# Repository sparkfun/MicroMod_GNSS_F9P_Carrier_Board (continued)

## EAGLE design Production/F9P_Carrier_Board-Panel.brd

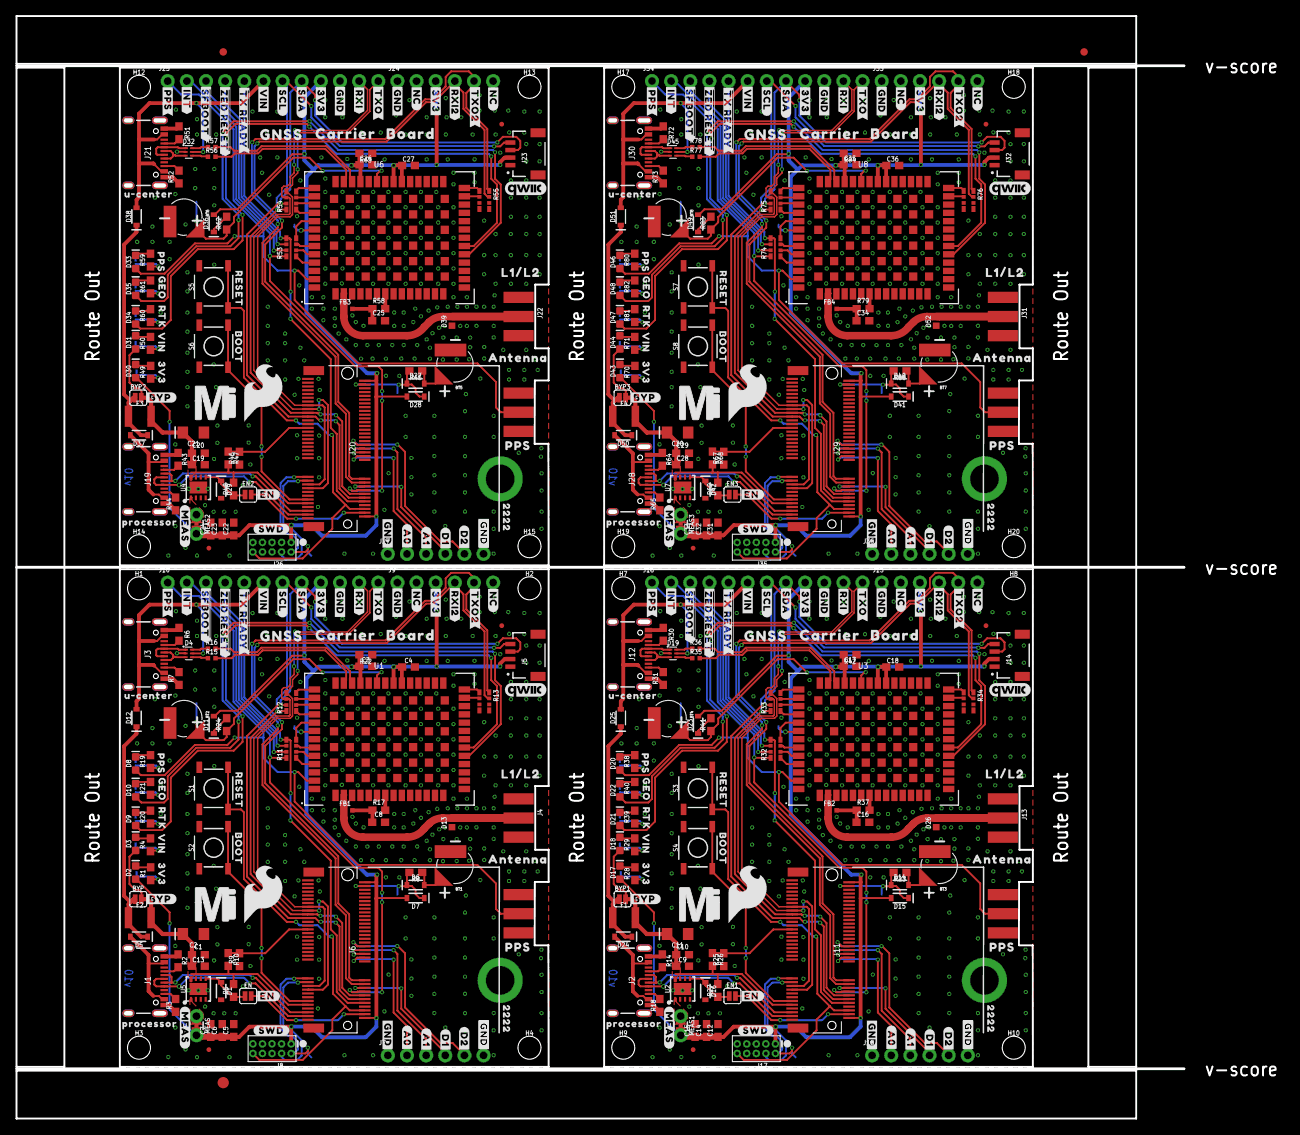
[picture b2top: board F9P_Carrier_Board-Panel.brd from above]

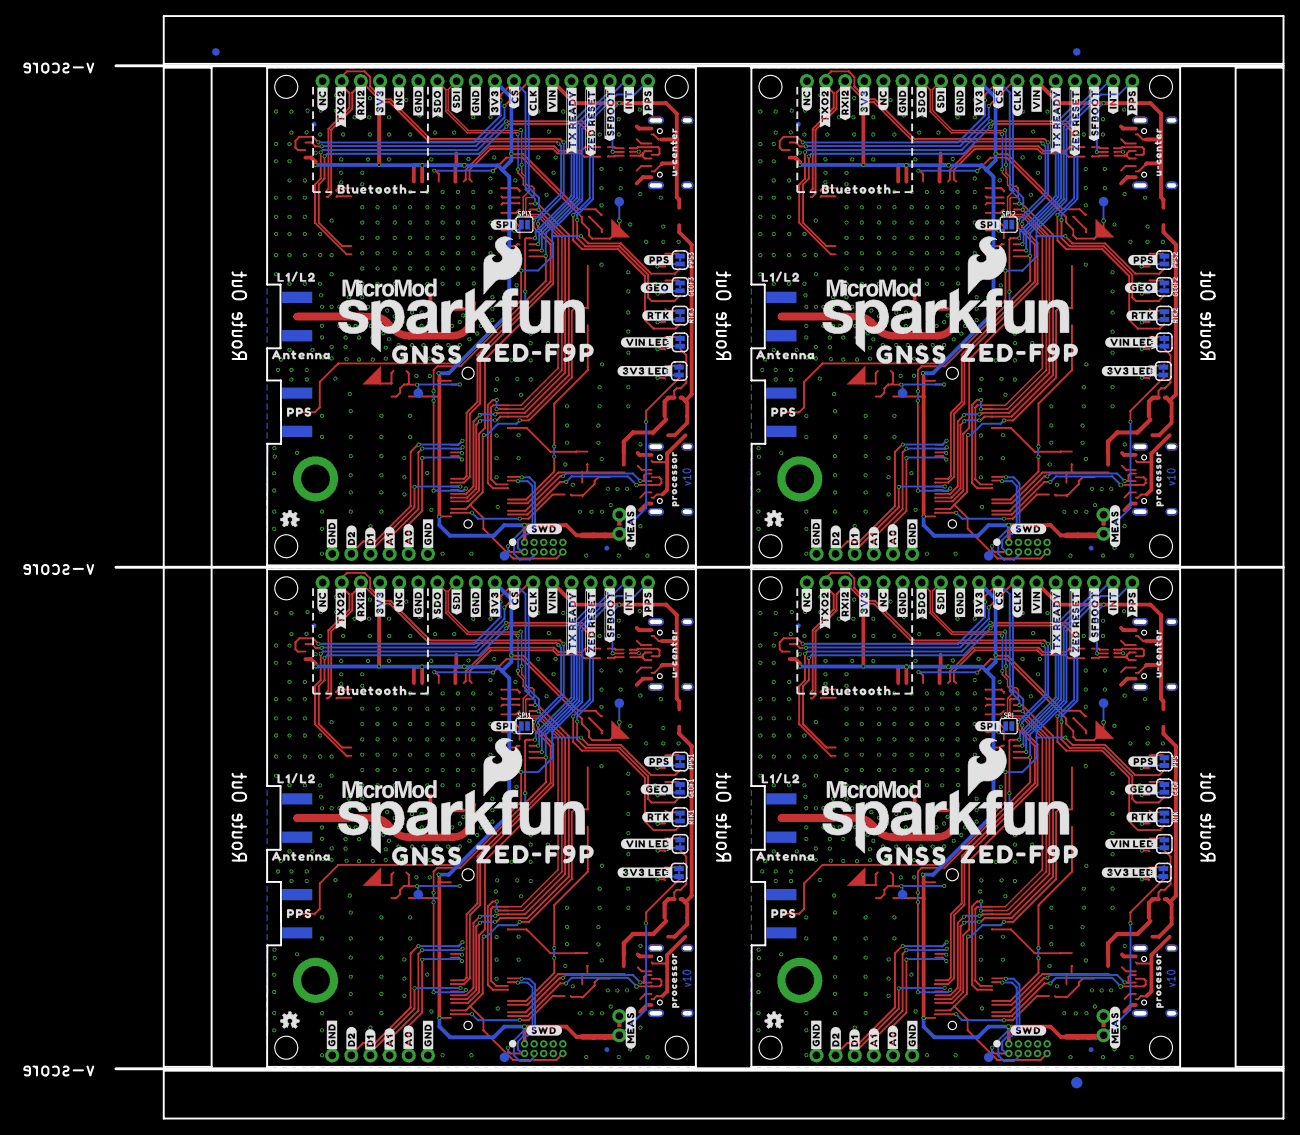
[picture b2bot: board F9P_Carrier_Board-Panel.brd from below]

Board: 2 copper layers, 154.9 x 146.3 mm, 698 parts (219 on the bottom side), 284 nets.

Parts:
3V1, 3V2, 3V3, 3V4: JUMPER-SMT_2_NC_TRACE_SILK; SMT-JUMPER_2_NC_TRACE_SILK
BT1, BT3, BT5, BT7: ML414H; ML414H_IV01E
BT2, BT4, BT6, BT8: ML414H_IV01E_BATTERY; ML414H_IV01E
BYP, BYP1, BYP2, BYP3: JUMPER-SMT_2_NO_SILK; SMT-JUMPER_2_NO_SILK
C1, C3, C4, C6, C10, C14, C17, C18, C20, C23, C26, C27, C29, C32, C35, C36: 0.1uF; 0603
C2, C11, C21, C30: 10uF; EIA3216
C5, C12, C22, C31: 1.0uF; 0603
C7, C9, C13, C15, C19, C24, C28, C33: 0.22uF; 0603
C8, C16, C25, C34: 47pF; 0603
D1, D16, D29, D42: 3.3V; SOD-323
D2, D3, D17, D18, D30, D31, D43, D44: RED; LED-0603
D4, D19, D32, D45: PRTR5V0U2F; SOT886
D5, D6, D12, D14, D24, D25, D27, D37, D38, D40, D50, D51: 3A/10V/280mV; SOD-323
D7, D15, D28, D41: 1A/23V/620mV; SOD-323
D8, D9, D10, D20, D21, D22, D33, D34, D35, D46, D47, D48: BLUE; LED-0603
D11, D23, D36, D49: 0.5A/40V/420mV; SOD-323
D13, D26, D39, D52: PESD0402; 0402
E1, E2, E3, E4: ANTENNA-SMA-GROUNDEDEDGE_SMA; SMA-EDGE
E$1, E$2, E$3, E$4: FIDUCIAL-1X2
E$5, E$6: FIDUCIAL-1.5X3
EN, EN1, EN2, EN3: JUMPER-SMT_2_NO_SILK; SMT-JUMPER_2_NO_SILK
F1, F2, F3, F4: 6V/2A; 1210
FB1, FB2, FB3, FB4: FERRITE_BEAD-120_OHM-0402T; 0402-TIGHT
FD1, FD2, FD3, FD4, FD5, FD6, FD7, FD8, FD9, FD10, FD11, FD12, FD13, FD14, FD15, FD16: FIDUCIALUFIDUCIAL; FIDUCIAL-MICRO
GEOF, GEOF1, GEOF2, GEOF3: JUMPER-SMT_2_NC_TRACE_SILK; SMT-JUMPER_2_NC_TRACE_SILK
H1, H2, H3, H4, H7, H8, H9, H10, H12, H13, H14, H15, H17, H18, H19, H20: STAND-OFFTIGHT; STAND-OFF-TIGHT
H5, H6, H11, H16: STAND-OFF-REFLOW-M2.5_2.5MM_TALL; STAND-OFF-REFLOW-M2.5
J1, J2, J3, J12, J19, J21, J28, J30: USB-C-16P-2LAYER-PADS
J4, J13, J22, J31: U.FL; SMA-EDGE
J5, J14, J23, J32: QWIIC_RIGHT_ANGLE; JST04_1MM_RA
J6, J11, J20, J29: MICROMOD-2222-C; M.2-CONNECTOR-E
J7, J9, J15, J18, J24, J27, J33, J36: 1X06_NO_SILK
J8, J17, J26, J35: JTAG; 2X5-PTH-1.27MM
J10, J16, J25, J34: 1X12_NO_SILK
LOGO1, LOGO4, LOGO6, LOGO8: SFE_LOGO_NAME_FLAME.3_INCH; SFE_LOGO_NAME_FLAME_.3
LOGO2, LOGO3, LOGO5, LOGO7: OSHW-LOGOMINI; OSHW-LOGO-MINI
MEAS, MEAS1, MEAS2, MEAS3: JUMPER-COMBO_2_NC_TRACE; COMBO-JUMPER_2_NC_TRACE
PPS, PPS1, PPS2, PPS3: JUMPER-SMT_2_NC_TRACE_SILK; SMT-JUMPER_2_NC_TRACE_SILK
R1, R4, R8, R19, R20, R21, R23, R28, R29, R38, R39, R40, R45, R49, R50, R59, R60, R61, R66, R70, R71, R80, R81, R82: 1k; 0603
R2, R3, R6, R7, R14, R18, R30, R31, R43, R44, R51, R52, R64, R65, R72, R73: 5.1k; 0603
R5, R22, R27, R42, R48, R63, R69, R84: 100k; 0603
R9, R25, R46, R67: 10k; 0603
R10, R26, R47, R68: 20k; 0603
R11, R12, R13, R32, R33, R34, R53, R54, R55, R74, R75, R76: 33; 1206_RA
R15, R16, R35, R36, R56, R57, R77, R78: 27OHM; 0402-TIGHT
R17, R37, R58, R79: 33; 0603
R24, R41, R62, R83: 3.3k; 0603
RTK, RTK1, RTK2, RTK3: JUMPER-SMT_2_NC_TRACE_SILK; SMT-JUMPER_2_NC_TRACE_SILK
S1, S3, S5, S7: Reset; TACTILE_SWITCH_SMD_5.2MM
S2, S4, S6, S8: BOOT; TACTILE_SWITCH_SMD_5.2MM
SPI, SPI1, SPI2, SPI3: JUMPER-SMT_2_NO_SILK; SMT-JUMPER_2_NO_SILK
TP1, TP2, TP3, TP4, TP5, TP6, TP7, TP8, TP9, TP10, TP11, TP12: TEST-POINT3X5; PAD.03X.05
U1, U3, U6, U8: U-BLOX_ZED-F9P; ZED-F9P
U2, U4, U5, U7: AP7361C-33; UDFN-8
U$1, U$150, U$239, U$328: ##SFBOOT##13
U$2, U$151, U$240, U$329: ##SFBOOT##8
U$3, U$4, U$31, U$32, U$98, U$99, U$113, U$114, U$191, U$192, U$206, U$207, U$280, U$281, U$295, U$296: #3V3#1
U$5, U$87, U$180, U$269: #RESET10
U$6, U$7, U$33, U$34, U$64, U$65, U$66, U$77, U$78, U$100, U$101, U$115, U$116, U$155, U$156, U$157, U$168, U$169, U$193, U$194, U$208, U$209, U$244, U$245, U$246, U$257, U$258, U$282, U$283, U$297, U$298, U$333, U$334, U$335, U$346, U$347: #GND#0
U$8, U$119, U$212, U$301: ##TX_READY##13
U$9, U$102, U$195, U$284: #PPS#6
U$10, U$128, U$221, U$310: #SCL#1
U$11, U$103, U$196, U$285: #RXI2#9
U$12, U$129, U$222, U$311: #SDA#0
U$13, U$130, U$223, U$312: #TXO#5
U$14, U$135, U$224, U$313: #RXI#6
U$15, U$104, U$197, U$286: #TXO2#9
U$16, U$136, U$225, U$314: PPS15
U$17, U$35, U$105, U$117, U$198, U$210, U$287, U$299: #VIN#13
U$18, U$106, U$199, U$288: GEO15
U$19, U$107, U$200, U$289: PPS14
U$20, U$108, U$201, U$290: RTK16
U$21, U$137, U$226, U$315: ANTENNA16
U$22, U$138, U$227, U$316: L1#L216
U$23, U$109, U$202, U$291: #GEO#9
U$24, U$120, U$213, U$302: ##TX_READY##7
U$25, U$152, U$241, U$330: MICROMOD_LOGO_.5
U$26, U$110, U$203, U$292: #PPS#10
U$27, U$111, U$204, U$293: #RTK#8
U$28, U$139, U$228, U$317: ##CS##9
U$29, U$121, U$214, U$303: #INT#4
U$30, U$112, U$205, U$294: #SPI#11
U$36, U$118, U$211, U$300: #INT#10
U$37, U$122, U$215, U$304: #PPS#3
U$38, U$123, U$216, U$305: #TXO2#10
U$39, U$86, U$179, U$268: #BYP#8
U$40, U$124, U$217, U$306: #RXI2#10
U$41, U$153, U$242, U$331: MICROMOD_MI_LOGO_1
U$42, U$89, U$94, U$132, U$182, U$187, U$271, U$276: #MEAS#10
U$43, U$88, U$181, U$270: BOOT10
U$44, U$125, U$218, U$307: ZED#F9P19
U$45, U$170, U$259, U$348: GNSS21
U$46, U$140, U$229, U$318: #CLK#7
U$47, U$141, U$230, U$319: #SDO#9
U$48, U$97, U$190, U$279: #EN#0
U$49, U$126, U$219, U$308: U#CENTER20
U$50, U$127, U$220, U$309: QWIIC_5.5MM
U$51, U$90, U$93, U$131, U$183, U$186, U$272, U$275: #SWD#10
U$52, U$73, U$162, U$163, U$251, U$252, U$340, U$341: PROCESSOR23
U$53, U$142, U$231, U$320: #SDI#11
U$54, U$143, U$232, U$321: BLUETOOTH24
U$55, U$83, U$175, U$176, U$264, U$265, U$353, U$354: #NC#4
U$56, U$144, U$233, U$322: U#CENTER22
U$57, U$164, U$253, U$342: #A0#14
U$58, U$145, U$234, U$323: L1#L217
U$59, U$146, U$235, U$324: ANTENNA17
U$60, U$147, U$236, U$325: PPS16
U$61, U$148, U$237, U$326: ##ZED_RESET##9
U$62, U$149, U$238, U$327: ##ZED_RESET##14
U$63, U$154, U$243, U$332: SFE_LOGO_FLAME_.3
U$67, U$158, U$247, U$336: #A0#8
U$68, U$91, U$184, U$273: VIN3
U$69, U$92, U$185, U$274: 3V34
U$70, U$159, U$248, U$337: #A1#8
U$71, U$160, U$249, U$338: #D1#8
U$72, U$161, U$250, U$339: #D2#8
U$74, U$165, U$254, U$343: #A1#14
U$75, U$166, U$255, U$344: #D1#14
U$76, U$167, U$256, U$345: #D2#14
U$79, U$171, U$260, U$349: GNSS501
U$80, U$172, U$261, U$350: CARRIER502
U$81, U$173, U$262, U$351: BOARD503
U$82, U$174, U$263, U$352: 2222501
U$84, U$85, U$177, U$178, U$266, U$267, U$355, U$356: #NC#5
U$95, U$133, U$188, U$277: #VIN_LED#10
U$96, U$134, U$189, U$278: #3V3_LED#10
VIN, VIN1, VIN2, VIN3: JUMPER-SMT_2_NC_TRACE_SILK; SMT-JUMPER_2_NC_TRACE_SILK

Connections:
3.3V: C3.1, C4.1, C5.1, C6.1, C7.1, D2.A, D7.A, D11.A, J5.2, J6.2, J6.74, J8.1, J9.3, J10.9, MEAS.2, MEAS.4, R22.2, U1.33, U1.34, U1.38
3.3V1: C12.1, C14.1, C15.1, C17.1, C18.1, D15.A, D17.A, D23.A, J11.2, J11.74, J14.2, J15.3, J16.9, J17.1, MEAS1.2, MEAS1.4, R42.2, U3.33, U3.34, U3.38
3.3V2: C22.1, C23.1, C24.1, C26.1, C27.1, D28.A, D30.A, D36.A, J20.2, J20.74, J23.2, J24.3, J25.9, J26.1, MEAS2.2, MEAS2.4, R63.2, U6.33, U6.34, U6.38
3.3V3: C31.1, C32.1, C33.1, C35.1, C36.1, D41.A, D43.A, D49.A, J29.2, J29.74, J32.2, J33.3, J34.9, J35.1, MEAS3.2, MEAS3.4, R84.2, U8.33, U8.34, U8.38
3.3V_EN: D1.C, EN.1, R5.1, U5.5
3.3V_EN1: D16.C, EN1.1, R27.1, U2.5
3.3V_EN2: D29.C, EN2.1, R48.1, U4.5
3.3V_EN3: D42.C, EN3.1, R69.1, U7.5
!BOOT!: J6.11, S2.3, S2.4
!BOOT!1: J11.11, S4.3, S4.4
!BOOT!2: J20.11, S6.3, S6.4
!BOOT!3: J29.11, S8.3, S8.4
!RESET!: J6.6, J8.10, S1.3, S1.4
!RESET!1: J11.6, J17.10, S3.3, S3.4
!RESET!2: J20.6, J26.10, S5.3, S5.4
!RESET!3: J29.6, J35.10, S7.3, S7.4
!SAFEBOOT!: J10.3, R11.P7
!SAFEBOOT!1: J16.3, R32.P7
!SAFEBOOT!2: J25.3, R53.P7
!SAFEBOOT!3: J34.3, R74.P7
!ZED_RESET!: J10.4, R11.P6
!ZED_RESET!1: J16.4, R32.P6
!ZED_RESET!2: J25.4, R53.P6
!ZED_RESET!3: J34.4, R74.P6
A0: J6.34, J7.2
A1: J6.38, J7.3
A2: J11.38, J18.3
A3: J11.34, J18.2
A4: J20.38, J27.3
A5: J20.34, J27.2
A6: J29.38, J36.3
A7: J29.34, J36.2
D1: J6.18, J7.4
D2: J11.18, J18.4
D3: J20.18, J27.4
D4: J29.18, J36.4
D_SEL: SPI.1, U1.47
D_SEL1: SPI1.1, U3.47
D_SEL2: SPI2.1, U6.47
D_SEL3: SPI3.1, U8.47
G0/D1: J11.40, J18.5
G0/D2: J6.40, J7.5
G0/D3: J20.40, J27.5
G0/D4: J29.40, J36.5
GEO_STAT: D10.A, U1.19
GEO_STAT1: D22.A, U3.19
GEO_STAT2: D35.A, U6.19
GEO_STAT3: D48.A, U8.19
GND: 3V3.2, BT1.-, BT2.-, C1.2, C2.-, C3.2, C4.2, C5.2, C6.2, C7.2, C8.2, C13.2, D1.A, D4.2, D13.1, E1.GND@0, E1.GND@1, E1.GND@2, E1.GND@3, GEOF.1, H5.1, J1.GND, J1.GND2, J3.GND, J3.GND2, J4.GND@0, J4.GND@1, J4.GND@2, J4.GND@3, J5.1, J6.1, J6.7, J6.33, J6.36, J6.39, J6.45, J6.75, J7.1, J7.6, J8.3, J8.5, J8.9, J9.1, J10.10, PPS.1, R2.1, R3.1, R6.1, R7.1, R9.1, R22.1, RTK.1, S1.1, S1.2, S2.1, S2.2, SPI.2, U1.1, U1.3, U1.12, U1.14, U1.32, U1.37, U1.41, U1.48, U1.55, U1.56, U1.57, U1.58, U1.59, U1.60, U1.61, U1.62, U1.63, U1.64, U1.65, U1.66, U1.67, U1.68, U1.69, U1.70, U1.71, U1.72, U1.73, U1.74, U1.75, U1.76, U1.77, U1.78, U1.79, U1.80, U1.81, U1.82, U1.83, U1.84, U1.85, U1.86, U1.87, U1.88, U1.89, U1.90, U1.91, U1.92, U1.93, U1.94, U1.95, U1.96, U1.97, U1.98, U1.99, U1.100, U1.101, U1.102, U5.4, U5.EP, VIN.2
GND1: 3V1.2, BT3.-, BT4.-, C9.2, C10.2, C11.-, C12.2, C14.2, C15.2, C16.2, C17.2, C18.2, D16.A, D19.2, D26.1, E2.GND@0, E2.GND@1, E2.GND@2, E2.GND@3, GEOF1.1, H6.1, J2.GND, J2.GND2, J11.1, J11.7, J11.33, J11.36, J11.39, J11.45, J11.75, J12.GND, J12.GND2, J13.GND@0, J13.GND@1, J13.GND@2, J13.GND@3, J14.1, J15.1, J16.10, J17.3, J17.5, J17.9, J18.1, J18.6, PPS1.1, R14.1, R18.1, R25.1, R30.1, R31.1, R42.1, RTK1.1, S3.1, S3.2, S4.1, S4.2, SPI1.2, U2.4, U2.EP, U3.1, U3.3, U3.12, U3.14, U3.32, U3.37, U3.41, U3.48, U3.55, U3.56, U3.57, U3.58, U3.59, U3.60, U3.61, U3.62, U3.63, U3.64, U3.65, U3.66, U3.67, U3.68, U3.69, U3.70, U3.71, U3.72, U3.73, U3.74, U3.75, U3.76, U3.77, U3.78, U3.79, U3.80, U3.81, U3.82, U3.83, U3.84, U3.85, U3.86, U3.87, U3.88, U3.89, U3.90, U3.91, U3.92, U3.93, U3.94, U3.95, U3.96, U3.97, U3.98, U3.99, U3.100, U3.101, U3.102, VIN1.2
GND2: 3V2.2, BT5.-, BT6.-, C19.2, C20.2, C21.-, C22.2, C23.2, C24.2, C25.2, C26.2, C27.2, D29.A, D32.2, D39.1, E3.GND@0, E3.GND@1, E3.GND@2, E3.GND@3, GEOF2.1, H11.1, J19.GND, J19.GND2, J20.1, J20.7, J20.33, J20.36, J20.39, J20.45, J20.75, J21.GND, J21.GND2, J22.GND@0, J22.GND@1, J22.GND@2, J22.GND@3, J23.1, J24.1, J25.10, J26.3, J26.5, J26.9, J27.1, J27.6, PPS2.1, R43.1, R44.1, R46.1, R51.1, R52.1, R63.1, RTK2.1, S5.1, S5.2, S6.1, S6.2, SPI2.2, U4.4, U4.EP, U6.1, U6.3, U6.12, U6.14, U6.32, U6.37, U6.41, U6.48, U6.55, U6.56, U6.57, U6.58, U6.59, U6.60, U6.61, U6.62, U6.63, U6.64, U6.65, U6.66, U6.67, U6.68, U6.69, U6.70, U6.71, U6.72, U6.73, U6.74, U6.75, U6.76, U6.77, U6.78, U6.79, U6.80, U6.81, U6.82, U6.83, U6.84, U6.85, U6.86, U6.87, U6.88, U6.89, U6.90, U6.91, U6.92, U6.93, U6.94, U6.95, U6.96, U6.97, U6.98, U6.99, U6.100, U6.101, U6.102, VIN2.2
GND3: 3V4.2, BT7.-, BT8.-, C28.2, C29.2, C30.-, C31.2, C32.2, C33.2, C34.2, C35.2, C36.2, D42.A, D45.2, D52.1, E4.GND@0, E4.GND@1, E4.GND@2, E4.GND@3, GEOF3.1, H16.1, J28.GND, J28.GND2, J29.1, J29.7, J29.33, J29.36, J29.39, J29.45, J29.75, J30.GND, J30.GND2, J31.GND@0, J31.GND@1, J31.GND@2, J31.GND@3, J32.1, J33.1, J34.10, J35.3, J35.5, J35.9, J36.1, J36.6, PPS3.1, R64.1, R65.1, R67.1, R72.1, R73.1, R84.1, RTK3.1, S7.1, S7.2, S8.1, S8.2, SPI3.2, U7.4, U7.EP, U8.1, U8.3, U8.12, U8.14, U8.32, U8.37, U8.41, U8.48, U8.55, U8.56, U8.57, U8.58, U8.59, U8.60, U8.61, U8.62, U8.63, U8.64, U8.65, U8.66, U8.67, U8.68, U8.69, U8.70, U8.71, U8.72, U8.73, U8.74, U8.75, U8.76, U8.77, U8.78, U8.79, U8.80, U8.81, U8.82, U8.83, U8.84, U8.85, U8.86, U8.87, U8.88, U8.89, U8.90, U8.91, U8.92, U8.93, U8.94, U8.95, U8.96, U8.97, U8.98, U8.99, U8.100, U8.101, U8.102, VIN3.2
INT: J6.16, J10.2, R11.P8
INT1: J11.16, J16.2, R32.P8
INT2: J20.16, J25.2, R53.P8
INT3: J29.16, J34.2, R74.P8
unnamed: D2.C, R1.2
unnamed: R4.1, VIN.1
unnamed: 3V3.1, R1.1
unnamed: D3.C, R4.2
unnamed: EN.2, J6.4
unnamed: J3.A5, R6.2
unnamed: J3.B5, R7.2
unnamed: R20.1, RTK.2
unnamed: D4.6, R16.1
unnamed: J1.A5, R2.2
unnamed: J1.B5, R3.2
unnamed: D4.3, J3.A6, J3.B6
unnamed: D4.1, J3.A7, J3.B7
unnamed: BT1.+, D6.A, R8.1
unnamed: R11.P1, U1.51
unnamed: R11.P2, U1.50
unnamed: D4.4, R15.1
unnamed: C8.1, FB1.2, R17.1
unnamed: R11.P3, U1.49
unnamed: R11.P4, U1.46
unnamed: R12.P1, U1.45
unnamed: R12.P2, U1.44
unnamed: R12.P3, U1.43
unnamed: R12.P4, U1.42
unnamed: R13.P1, U1.27
unnamed: R13.P2, U1.26
unnamed: PPS.2, R19.1
unnamed: D8.C, R19.2
unnamed: D9.C, R20.2
unnamed: J2.A5, R14.2
unnamed: J2.B5, R18.2
unnamed: D11.C, R24.2
unnamed: BT3.+, D14.A, R23.1
unnamed: EN1.2, J11.4
unnamed: J12.A5, R30.2
unnamed: J12.B5, R31.2
unnamed: D19.3, J12.A6, J12.B6
unnamed: D19.1, J12.A7, J12.B7
unnamed: R34.P1, U3.27
unnamed: R34.P2, U3.26
unnamed: C16.1, FB2.2, R37.1
unnamed: R39.1, RTK1.2
unnamed: PPS1.2, R38.1
unnamed: D20.C, R38.2
unnamed: GEOF.2, R21.1
unnamed: D10.C, R21.2
unnamed: D21.C, R39.2
unnamed: GEOF1.2, R40.1
unnamed: D22.C, R40.2
unnamed: D23.C, R41.2
unnamed: D17.C, R28.2
unnamed: 3V1.1, R28.1
unnamed: R29.1, VIN1.1
unnamed: D18.C, R29.2
unnamed: R33.P1, U3.45
unnamed: R33.P2, U3.44
unnamed: R33.P3, U3.43
unnamed: R33.P4, U3.42
unnamed: R32.P1, U3.51
unnamed: R32.P2, U3.50
unnamed: R32.P3, U3.49
unnamed: R32.P4, U3.46
unnamed: D19.6, R36.1
unnamed: D19.4, R35.1
unnamed: J19.A5, R43.2
unnamed: J19.B5, R44.2
unnamed: BT5.+, D27.A, R45.1
unnamed: EN2.2, J20.4
unnamed: J21.A5, R51.2
unnamed: J21.B5, R52.2
unnamed: D32.3, J21.A6, J21.B6
unnamed: D32.1, J21.A7, J21.B7
unnamed: R55.P1, U6.27
unnamed: R55.P2, U6.26
unnamed: C25.1, FB3.2, R58.1
unnamed: R60.1, RTK2.2
unnamed: PPS2.2, R59.1
unnamed: D33.C, R59.2
unnamed: D34.C, R60.2
unnamed: GEOF2.2, R61.1
unnamed: D35.C, R61.2
unnamed: D36.C, R62.2
unnamed: D30.C, R49.2
unnamed: 3V2.1, R49.1
unnamed: R50.1, VIN2.1
unnamed: D31.C, R50.2
unnamed: R54.P1, U6.45
unnamed: R54.P2, U6.44
unnamed: R54.P3, U6.43
unnamed: R54.P4, U6.42
unnamed: R53.P1, U6.51
unnamed: R53.P2, U6.50
unnamed: R53.P3, U6.49
unnamed: R53.P4, U6.46
unnamed: D32.6, R57.1
unnamed: D32.4, R56.1
unnamed: J28.A5, R64.2
unnamed: J28.B5, R65.2
unnamed: BT7.+, D40.A, R66.1
unnamed: EN3.2, J29.4
unnamed: J30.A5, R72.2
unnamed: J30.B5, R73.2
unnamed: D45.3, J30.A6, J30.B6
unnamed: D45.1, J30.A7, J30.B7
unnamed: R76.P1, U8.27
unnamed: R76.P2, U8.26
unnamed: C34.1, FB4.2, R79.1
unnamed: R81.1, RTK3.2
unnamed: PPS3.2, R80.1
unnamed: D46.C, R80.2
unnamed: D47.C, R81.2
unnamed: GEOF3.2, R82.1
unnamed: D48.C, R82.2
unnamed: D49.C, R83.2
unnamed: D43.C, R70.2
unnamed: 3V4.1, R70.1
unnamed: R71.1, VIN3.1
unnamed: D44.C, R71.2
unnamed: R75.P1, U8.45
unnamed: R75.P2, U8.44
unnamed: R75.P3, U8.43
unnamed: R75.P4, U8.42
unnamed: R74.P1, U8.51
unnamed: R74.P2, U8.50
unnamed: R74.P3, U8.49
unnamed: R74.P4, U8.46
unnamed: D45.6, R78.1
unnamed: D45.4, R77.1
OUT_MEAS: MEAS.1, MEAS.3, U5.1
OUT_MEAS1: MEAS1.1, MEAS1.3, U2.1
OUT_MEAS2: MEAS2.1, MEAS2.3, U4.1
OUT_MEAS3: MEAS3.1, MEAS3.3, U7.1
PPS: D8.A, E1.SIG, J10.1, U1.53
PPS1: D20.A, E2.SIG, J16.1, U3.53
PPS2: D33.A, E3.SIG, J25.1, U6.53
PPS3: D46.A, E4.SIG, J34.1, U8.53
RF_IN: D13.2, FB1.1, J4.SIG, U1.2
RF_IN1: D26.2, FB2.1, J13.SIG, U3.2
RF_IN2: D39.2, FB3.1, J22.SIG, U6.2
RF_IN3: D52.2, FB4.1, J31.SIG, U8.2
RTC_3V: D6.C, D7.C, J6.72, R8.2, TP1.1
RTC_3V1: D14.C, D15.C, J11.72, R23.2, TP4.1
RTC_3V2: D27.C, D28.C, J20.72, R45.2, TP7.1
RTC_3V3: D40.C, D41.C, J29.72, R66.2, TP10.1
RTK_STAT: D9.A, U1.20
RTK_STAT1: D21.A, U3.20
RTK_STAT2: D34.A, U6.20
RTK_STAT3: D47.A, U8.20
RXI1: J11.22, J15.4, R34.P7
RXI2: J6.22, J9.4, R13.P7
RXI3: J20.22, J24.4, R55.P7
RXI4: J29.22, J33.4, R76.P7
RXI/SDI: J6.17, J6.59, J10.11, R12.P6
RXI/SDI1: J11.17, J11.59, J16.11, R33.P6
RXI/SDI2: J20.17, J20.59, J25.11, R54.P6
RXI/SDI3: J29.17, J29.59, J34.11, R75.P6
SCL/SCK: J5.4, J6.14, J6.57, J10.7, R12.P8
SCL/SCK1: J11.14, J11.57, J14.4, J16.7, R33.P8
SCL/SCK2: J20.14, J20.57, J23.4, J25.7, R54.P8
SCL/SCK3: J29.14, J29.57, J32.4, J34.7, R75.P8
SDA/!CS!: J5.3, J6.12, J6.55, J10.8, R12.P7
SDA/!CS!1: J11.12, J11.55, J14.3, J16.8, R33.P7
SDA/!CS!2: J20.12, J20.55, J23.3, J25.8, R54.P7
SDA/!CS!3: J29.12, J29.55, J32.3, J34.8, R75.P7
SWDCK: J6.21, J8.4
SWDCK1: J11.21, J17.4
SWDCK2: J20.21, J26.4
SWDCK3: J29.21, J35.4
SWDIO: J6.23, J8.2, TP2.1
SWDIO1: J11.23, J17.2, TP5.1
SWDIO2: J20.23, J26.2, TP8.1
SWDIO3: J29.23, J35.2, TP11.1
TXO1: J11.20, J15.5, R34.P8
TXO2: J6.20, J9.5, R13.P8
TXO3: J20.20, J24.5, R55.P8
TXO4: J29.20, J33.5, R76.P8
TXO/SDO: J6.19, J6.61, J10.12, R12.P5
TXO/SDO1: J11.19, J11.61, J16.12, R33.P5
TXO/SDO2: J20.19, J20.61, J25.12, R54.P5
TXO/SDO3: J29.19, J29.61, J34.12, R75.P5
TX_READY: J6.10, J10.5, R11.P5
TX_READY1: J11.10, J16.5, R32.P5
TX_READY2: J20.10, J25.5, R53.P5
TX_READY3: J29.10, J34.5, R74.P5
USB_N: J1.A7, J1.B7, J6.5
USB_N1: J2.A7, J2.B7, J11.5
USB_N2: J19.A7, J19.B7, J20.5
USB_N3: J28.A7, J28.B7, J29.5
USB_P: J1.A6, J1.B6, J6.3
USB_P1: J2.A6, J2.B6, J11.3
USB_P2: J19.A6, J19.B6, J20.3
USB_P3: J28.A6, J28.B6, J29.3
VIN: BYP.2, C1.1, C2.+, C13.1, D3.A, F2.2, J6.9, R5.2, R10.2, U5.8
VIN1: BYP1.2, C9.1, C10.1, C11.+, D18.A, F1.2, J11.9, R26.2, R27.2, U2.8
VIN2: BYP2.2, C19.1, C20.1, C21.+, D31.A, F3.2, J20.9, R47.2, R48.2, U4.8
VIN3: BYP3.2, C28.1, C29.1, C30.+, D44.A, F4.2, J29.9, R68.2, R69.2, U7.8
VIN/1: J11.49, R25.2, R26.1
VIN/2: J20.49, R46.2, R47.1
VIN/3: J6.49, R9.2, R10.1
VIN/4: J29.49, R67.2, R68.1
V_BATT: BT2.+, R24.1, TP3.1, U1.36
V_BATT1: BT4.+, R41.1, TP6.1, U3.36
V_BATT2: BT6.+, R62.1, TP9.1, U6.36
V_BATT3: BT8.+, R83.1, TP12.1, U8.36
V_FUSE: BYP.1, D5.C, D12.C, F2.1
V_FUSE1: BYP1.1, D24.C, D25.C, F1.1
V_FUSE2: BYP2.1, D37.C, D38.C, F3.1
V_FUSE3: BYP3.1, D50.C, D51.C, F4.1
V_RF: R17.2, U1.7
V_RF1: R37.2, U3.7
V_RF2: R58.2, U6.7
V_RF3: R79.2, U8.7
V_USB: D5.A, J1.VBUS1, J1.VBUS2
V_USB1: D24.A, J2.VBUS1, J2.VBUS2
V_USB2: D37.A, J19.VBUS1, J19.VBUS2
V_USB3: D50.A, J28.VBUS1, J28.VBUS2
V_USB_1: D19.5, D25.A, J12.VBUS1, J12.VBUS2, J16.6
V_USB_2: D4.5, D12.A, J3.VBUS1, J3.VBUS2, J10.6
V_USB_3: D32.5, D38.A, J21.VBUS1, J21.VBUS2, J25.6
V_USB_4: D45.5, D51.A, J30.VBUS1, J30.VBUS2, J34.6
ZED_USB_N: R16.2, U1.39
ZED_USB_N1: R36.2, U3.39
ZED_USB_N2: R57.2, U6.39
ZED_USB_N3: R78.2, U8.39
ZED_USB_P: R15.2, U1.40
ZED_USB_P1: R35.2, U3.40
ZED_USB_P2: R56.2, U6.40
ZED_USB_P3: R77.2, U8.40

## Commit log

2020-11-06 Initial commit - power M.2 connector
2020-11-06 Adds the F9R and the ESD protection diode
2020-11-20 Mostly finishes schematic
2020-11-20 Puts parts generally where they will be routed
2020-11-23 Still situating the parts within the board
2020-11-23 Moves parts to their final resting places (mostly)
2020-11-30 Routes more air wires - almost done
2020-12-01 Finishes initial routing
2020-12-01 Adds more vias to the design
2020-12-01 Adds even more vias
2020-12-03 Adds silk and measures
2020-12-07 Fixes nets on the ZED-F9P, fixes silk, removes excessive GND vias, adds SMA connector for PPS
    * Fixes 12 pin header
    * Fixes jumper labels in schematic
    * Fixes RX/TX lines, and SDO/SDI lines
    * Adds version number
2020-12-09 Fixes silk, updates schematic with better labels and descriptions
2020-12-09 Removes "INT" trace to MicroMod connector
2020-12-11 Adds micromod silk to the board, fixes zed reset silk
2020-12-11 Adds repo template, cams design for order
2020-12-14 Updates nets on the 100k at VREG, adds descpription of SPI jumper, adds VBAT testpoint
2021-01-07 Renames the erroneously named SCL/CLK net to SCLK/SCK
    * Reroutes so that SCL and SCK are connected
2021-01-13 Rolls version to v10, moves some vias, deletes I2C_INT net (not used)
2021-01-13 Adjusts battery placement on board so that it's mostly out of the way
    * Breaks out a few general purpose pins to a 6 pin header at the bottom of the board
    * Adds text to led and enable jumpers
    * Adds text about interrupt
    * Adds connection from interrupt on ublox module to micromod connector.
    * Fixes "processor" silk
2021-01-14 Adds I2C address to schematic, swaps SMA connector to female version
2021-01-14 Adds production files - 2x2 panel
2021-01-15 Removes GPS silk, adds GNSS silk, repanelizes with new silk
2021-09-14 Adds diode protection to antenna
2021-09-15 Updates silk, moves 1x6 header to the left .005"
2021-09-16 Replaces SMD SMA connector with PTH one
2021-09-16 Updated panel
